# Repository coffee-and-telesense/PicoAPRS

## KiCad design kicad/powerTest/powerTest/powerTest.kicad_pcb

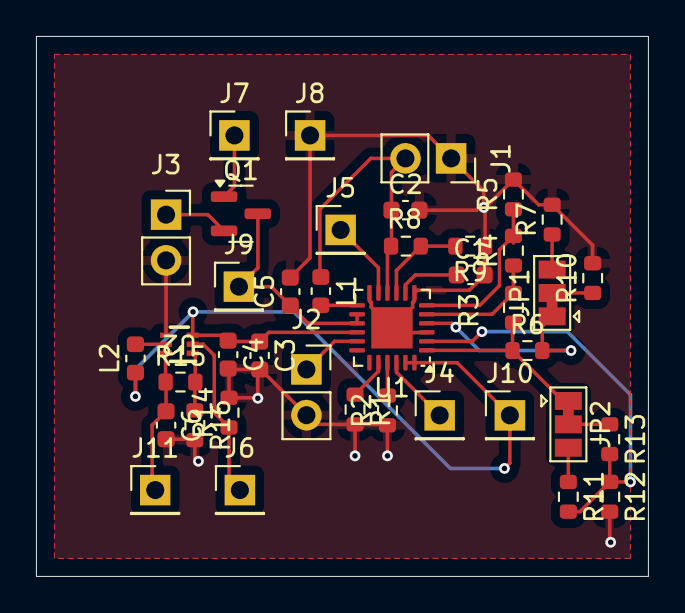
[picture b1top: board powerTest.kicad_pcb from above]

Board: 2 copper layers, 34.0 x 30.0 mm, 40 parts (0 on the bottom side), 27 nets.

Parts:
C1: 10n; C_0603_1608Metric
C2, C5, C6: 10u; C_0603_1608Metric
C3: 0.1u; C_0603_1608Metric
C4: 4.7u; C_0603_1608Metric
J1: Solar Panel; PinSocket_1x02_P2.54mm_Vertical
J2: BATT; PinSocket_1x02_P2.54mm_Vertical
J3: 3V3 Sensor Bus; PinSocket_1x02_P2.54mm_Vertical
J4, J5, J6, J7, J8, J9, J10, J11: Conn_01x01_Pin; PinHeader_1x01_P2.54mm_Vertical
JP1: Power Type Select; SolderJumper-3_P1.3mm_Bridged12_Pad1.0x1.5mm
JP2: PTS; SolderJumper-3_P1.3mm_Bridged12_Pad1.0x1.5mm
L1: 22u; L_0603_1608Metric
L2: 1u; L_0603_1608Metric
Q1: BSS84; SOT-23
R1: 55.6k; R_0603_1608Metric
R2: 150k; R_0603_1608Metric
R3: 6.98M; R_0603_1608Metric
R4: 499k; R_0603_1608Metric
R5: 2.67M; R_0603_1608Metric
R6: 7.15M; R_0603_1608Metric
R7: 8.45M; R_0603_1608Metric
R8: 4.7M; R_0603_1608Metric
R9: 18M; R_0603_1608Metric
R10: 4.32M; R_0603_1608Metric
R11: 9.76M; R_0603_1608Metric
R12: 4.99M; R_0603_1608Metric
R13: 10.2M; R_0603_1608Metric
R14: 10M; R_0603_1608Metric
R15: 1.47M; R_0603_1608Metric
R16: 200k; R_0603_1608Metric
U1: ADP5091; LFCSP-24-1EP_4x4mm_P0.5mm_EP2.3x2.3mm
U2: TPS61023DRLR; DRL0006A

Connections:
5V_EN: J6.1, R14.1, U2.2 (EN)
+3.3V: C5.1, J9.1, Q1.3 (D), U1.14 (REG_OUT), U1.15 (REG_FB)
+5V: C6.1, J11.1, R15.1, U2.6 (VOUT)
/SETSD: R11.2, R12.1, R13.2, U1.2 (SETSD)
GND: C1.2, C2.2, C3.2, C4.2, C5.2, C6.2, J1.1, J2.2, J3.2, J8.1, R1.2, R2.1, R5.2, R7.2, R9.1, R10.2, R12.2, R14.2, R16.2, U1.3 (SETBK), U1.7 (AGND), U1.12 (PGND), U1.25 (AGND), U2.4 (GND)
LLD: J5.1, U1.11 (LLD)
unnamed: C2.1, J1.2, L1.1, R8.1, U1.10 (VIN)
unnamed: J2.1, U1.17 (BAT)
unnamed: J3.1, Q1.2 (S)
unnamed: JP1.1 (A), R6.2, U1.4 (TERM)
unnamed: JP1.3 (B), R7.1
unnamed: JP1.2 (C), R10.1
unnamed: JP2.1 (A), R3.1, R6.1, U1.1 (REF)
unnamed: JP2.3 (B), R11.1
unnamed: JP2.2 (C), R13.1
unnamed: C1.1, U1.8 (CBP)
unnamed: R2.2, U1.21 (MINOP)
unnamed: R8.2, R9.2, U1.9 (MPPT)
unnamed: R4.2, R5.1, U1.6 (SETHYST)
unnamed: R3.2, R4.1, U1.5 (SETPG)
unnamed: L1.2, U1.13 (SW)
unnamed: R1.1, U1.20 (VID)
unnamed: R15.2, R16.1, U2.1 (FB)
unnamed: L2.2, U2.5 (SW)
VSS: C3.1, C4.1, J10.1, L2.1, U1.16 (SYS), U1.23 (REG_D1), U1.24 (REG_D0), U2.3 (VIN)
~CHRGR_EN: J4.1, U1.22 (DIS_SW)
~SNSR_EN: J7.1, Q1.1 (G)

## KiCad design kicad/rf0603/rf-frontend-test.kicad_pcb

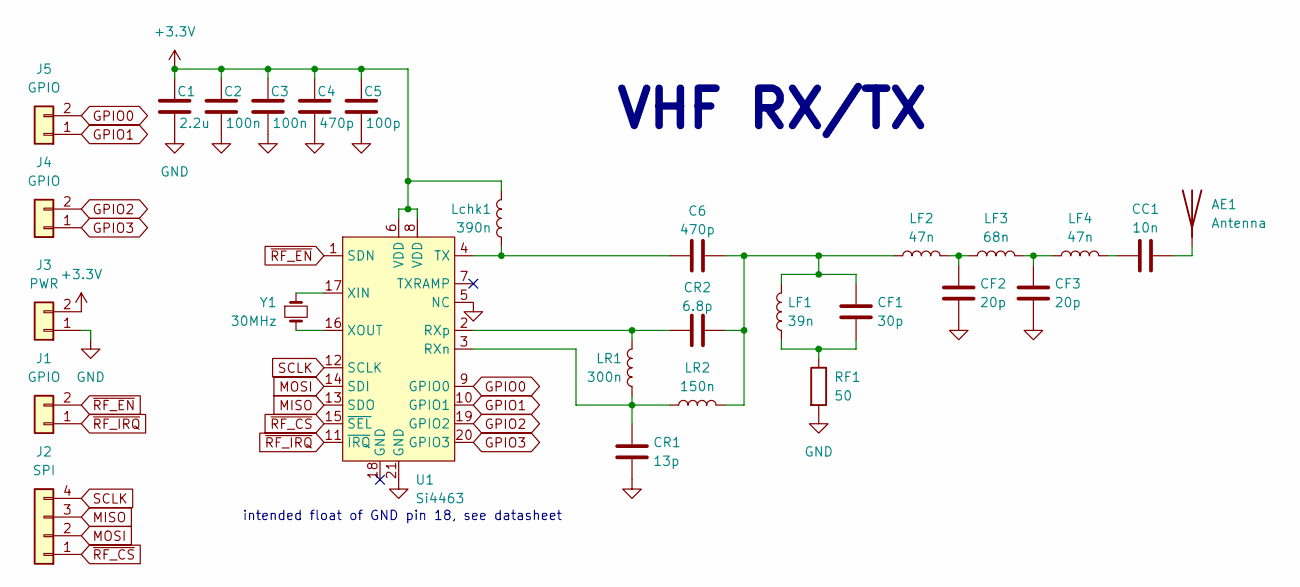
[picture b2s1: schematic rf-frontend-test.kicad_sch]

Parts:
AE1: Antenna; SolderWirePad_1x01_SMD_1x2mm
C1: 2.2u; C_0402_1005Metric
C2, C3: 100n; C_0402_1005Metric
C4, C6: 470p; C_0402_1005Metric
C5: 100p; C_0402_1005Metric
CC1: 10n; C_0402_1005Metric
CF1: 30p; C_0402_1005Metric
CF2, CF3: 20p; C_0402_1005Metric
CR1: 13p; C_0402_1005Metric
CR2: 6.8p; C_0402_1005Metric
J1, J4, J5: GPIO; PinHeader_1x02_P2.54mm_Vertical
J2: SPI; PinHeader_1x04_P2.54mm_Vertical
J3: PWR; PinHeader_1x02_P2.54mm_Vertical
LF1: 39n; L_0402_1005Metric
LF2, LF4: 47n; L_0402_1005Metric
LF3: 68n; L_0402_1005Metric
LR1: 300n; L_0402_1005Metric
LR2: 150n; L_0402_1005Metric
Lchk1: 390n; L_0402_1005Metric
RF1: 50; R_0402_1005Metric
U1: Si4463; QFN-20-1EP_4x4mm_P0.5mm_EP2.6x2.6mm
Y1: 30MHz; Crystal_SMD_Abracon_ABM3-2Pin_5.0x3.2mm

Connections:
+3.3V: C1.1, C2.1, C3.1, C4.1, C5.1, J3.2, Lchk1.1, U1.6 (VDD), U1.8 (VDD)
GND: C1.2, C2.2, C3.2, C4.2, C5.2, CF2.2, CF3.2, CR1.2, J3.1, RF1.2, U1.5 (NC), U1.21 (GND)
GPIO0: J5.2, U1.9 (GPIO0)
GPIO1: J5.1, U1.10 (GPIO1)
GPIO2: J4.2, U1.19 (GPIO2)
GPIO3: J4.1, U1.20 (GPIO3)
MISO: J2.3, U1.13 (SDO)
MOSI: J2.2, U1.14 (SDI)
unnamed: AE1.1 (A), CC1.2
unnamed: C6.2, CF1.1, CR2.2, LF1.2, LF2.1, LR2.2
unnamed: CC1.1, LF4.2
unnamed: CF1.2, LF1.1, RF1.1
unnamed: CF2.1, LF2.2, LF3.1
unnamed: CF3.1, LF3.2, LF4.1
unnamed: CR1.1, LR1.2, LR2.1, U1.3 (RXn)
unnamed: CR2.1, LR1.1, U1.2 (RXp)
unnamed: C6.1, Lchk1.2, U1.4 (TX)
unnamed: U1.17 (XIN), Y1.1
unnamed: U1.16 (XOUT), Y1.2
SCLK: J2.4, U1.12 (SCLK)
~RF_CS: J2.1, U1.15 (~SEL)
~RF_EN: J1.2, U1.1 (SDN)
~RF_IRQ: J1.1, U1.11 (~IRQ)

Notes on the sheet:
intended float of GND pin 18, see datasheet
VHF RX/TX

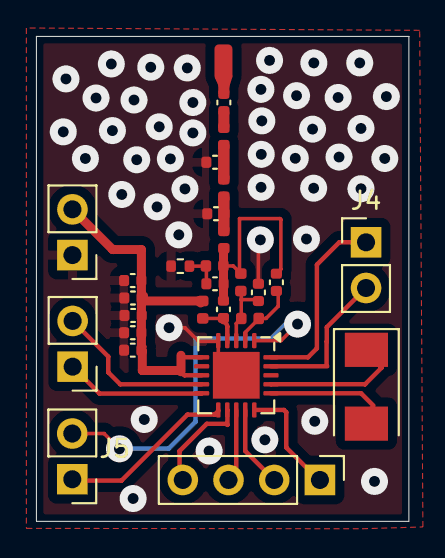
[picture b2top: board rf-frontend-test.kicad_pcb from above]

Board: 2 copper layers, 20.7 x 26.9 mm, 28 parts (0 on the bottom side), 23 nets.
